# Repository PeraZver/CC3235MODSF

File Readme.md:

# CC3235MODSF Demo Board

Based on the CC3235MODSF LaunchPad Dev Board. The board is based around WiFi module CC3235MODSF, that contains

 - CC3235F MCU
 - 40.0-MHz crystal
 - 32.768-kHz crystal (RTC)
 - 32-Mbit SPI serial flash

## Key features

 - Dual-Band WiFi module CC3235MODSF
 - Onboard 3V3 regulator TLV1117-33
 - Onboard chip antenna M830520 
 - 4-wire JTAG and 2-wire SWD interface
 - Micro-USB connector for power and serial connections over CP2102N
 - Boot mode DIP switch
 - Some LEDs and buttons

Pero, 5/2020

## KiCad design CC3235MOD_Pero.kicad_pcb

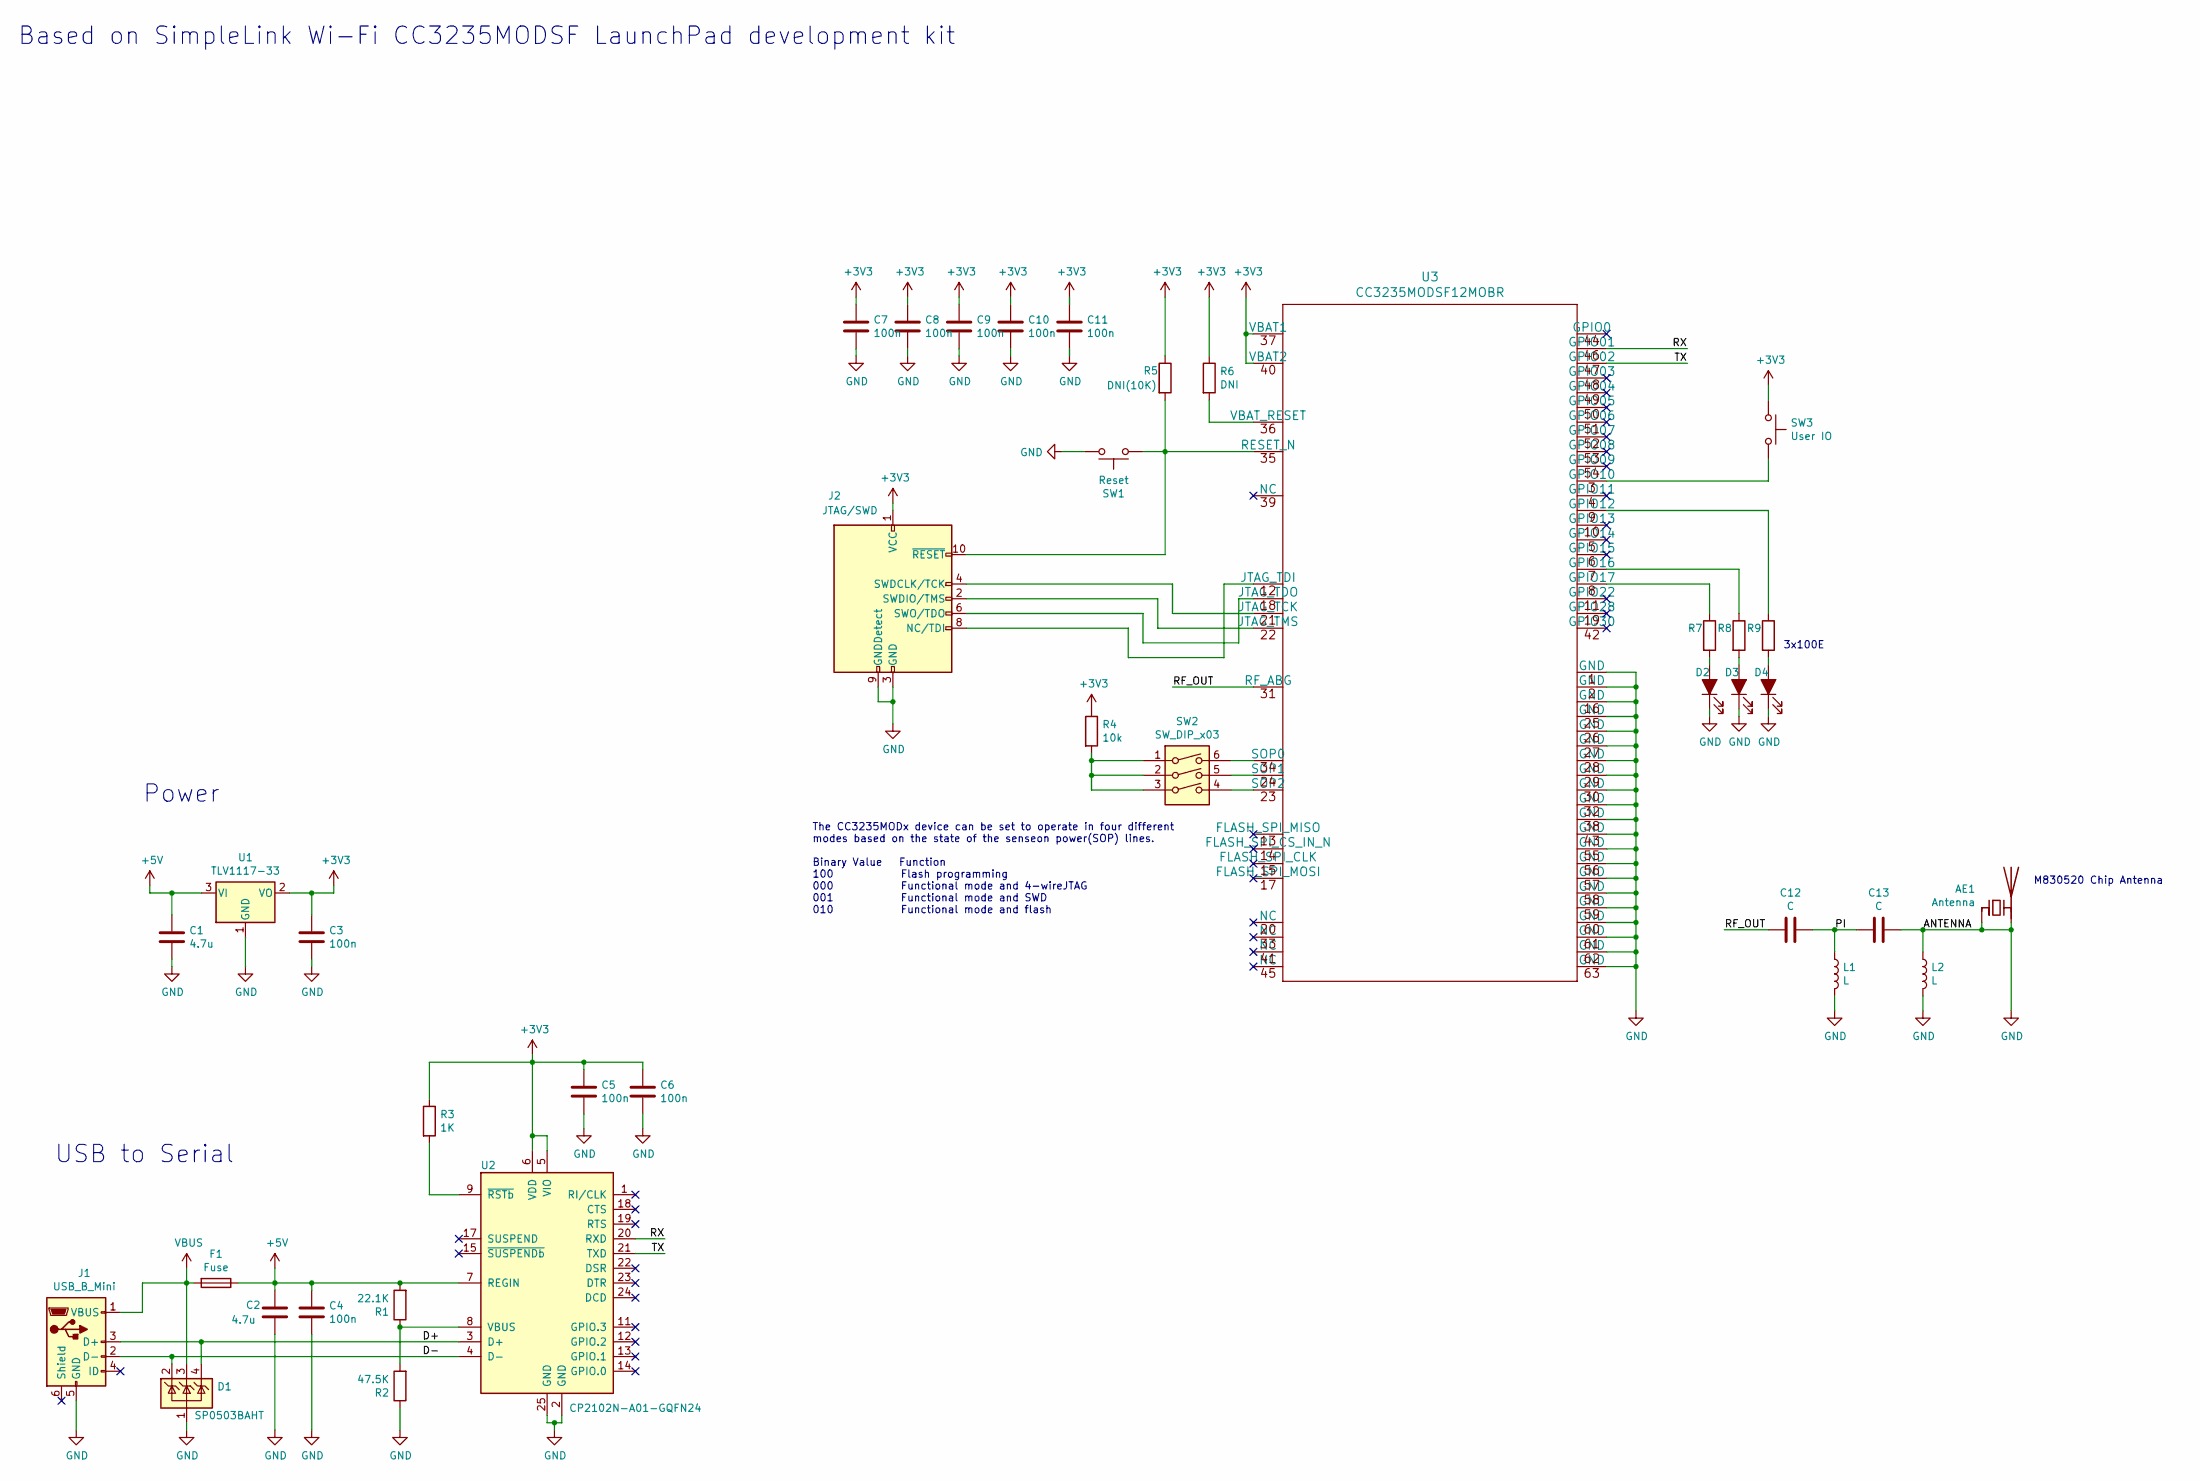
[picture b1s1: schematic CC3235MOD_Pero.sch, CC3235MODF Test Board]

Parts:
AE1: Antenna; M830520
C1, C2: 4.7u; C_0805
C3, C4, C5, C6, C7, C8, C9, C10, C11: 100n; C_0603
C12, C13: C; C_0603_1608Metric
D1: SP0503BAHT; SOT-143
D2, D3, D4: LED_ALT; LED_0603
F1: Fuse; Fuse_SMD1206_Reflow
J1: USB_B_Mini; USB_Micro-B_Molex-105017-0001
J2: JTAG/SWD; Pin_Header_Straight_2x05_Pitch2.54mm
L1, L2: L; L_0603
R1: 22.1K; R_0603
R2: 47.5K; R_0603
R3: 1K; R_0603
R4: 10k; R_0603
R5: DNI(10K); R_0603
R6: DNI; R_0603
R7, R8, R9: 100; R_0603
SW1: Reset; SW_SPST_EVQP0
SW2: SW_DIP_x03; SW_DIP_x3_W8.61mm_Slide_LowProfile
SW3: User IO; SW_SPST_EVQP0
U1: TLV1117-33; SOT-223-3_TabPin2
U2: CP2102N-A01-GQFN24; QFN-24-1EP_4x4mm_Pitch0.5mm
U3: CC3235MODSF12MOBR

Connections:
+3V3: C3.1, C5.1, C6.1, C7.1, C8.1, C9.1, C10.1, C11.1, J2.1 (VCC), R3.1, R4.1, R5.1, R6.1, SW3.1, U1.2 (VO), U2.5 (VIO), U2.6 (VDD), U3.37 (VBAT1), U3.40 (VBAT2)
+5V: C1.1, C2.1, C4.1, F1.1, R1.2, U1.3 (VI), U2.7 (REGIN)
/D+: D1.4 (K), J1.3 (D+), U2.3 (D+)
/D-: D1.2 (K), J1.2 (D-), U2.4 (D-)
/PI: C12.1, C13.2, L1.1
/RF_OUT: C12.2, U3.31 (RF_ABG)
/RX: U2.20 (RXD), U3.46 (GPIO01)
/TX: U2.21 (TXD), U3.47 (GPIO02)
GND: AE1.1 (FEED), AE1.2 (PCB_Trace), C1.2, C2.2, C3.2, C4.2, C5.2, C6.2, C7.2, C8.2, C9.2, C10.2, C11.2, C13.1, D1.1 (A), D2.1 (K), D3.1 (K), D4.1 (K), J1.5 (GND), J2.3 (GND), J2.5 (GND), J2.9 (GNDDetect), L1.2, L2.1, L2.2, R2.1, SW1.1, U1.1 (GND), U2.2 (GND), U2.25 (GND), U3.1 (GND), U3.2 (GND), U3.16 (GND), U3.25 (GND), U3.26 (GND), U3.27 (GND), U3.28 (GND), U3.29 (GND), U3.30 (GND), U3.32 (GND), U3.38 (GND), U3.43 (GND), U3.55 (GND), U3.56 (GND), U3.57 (GND), U3.58 (GND), U3.59 (GND), U3.60 (GND), U3.61 (GND), U3.62 (GND), U3.63 (GND), U3.V
unnamed: D2.2 (A), R7.2
unnamed: D3.2 (A), R8.2
unnamed: D4.2 (A), R9.2
unnamed: J2.2 (SWDIO/TMS), U3.22 (JTAG_TMS)
unnamed: J2.4 (SWDCLK/TCK), U3.21 (JTAG_TCK)
unnamed: J2.6 (SWO/TDO), U3.18 (JTAG_TDO)
unnamed: J2.8 (NC/TDI), U3.12 (JTAG_TDI)
unnamed: J2.10 (~RESET~), R5.2, SW1.2, U3.35 (RESET_N)
unnamed: R1.1, R2.2, U2.8 (VBUS)
unnamed: R3.2, U2.9 (~RSTb)
unnamed: R4.2, SW2.1, SW2.2, SW2.3
unnamed: R6.2, U3.36 (VBAT_RESET)
unnamed: R7.1, U3.8 (GPIO17)
unnamed: R8.1, U3.7 (GPIO16)
unnamed: R9.1, U3.9 (GPIO12)
unnamed: SW2.4, U3.23 (SOP2)
unnamed: SW2.5, U3.24 (SOP1)
unnamed: SW2.6, U3.34 (SOP0)
unnamed: SW3.2, U3.3 (GPIO10)
VBUS: D1.3 (K), F1.2, J1.1 (VBUS)

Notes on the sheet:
M830520 Chip Antenna
The CC3235MODx device can be set to operate in four different modes based on the state of the senseon power(SOP) lines. Binary Value Function 100 Flash programming 000 Functional mode and 4-wireJTAG 001 Functional mode and SWD 010 Functional mode and flash
Based on SimpleLink Wi-Fi CC3235MODSF LaunchPad development kit
USB to Serial
Power
3x100E

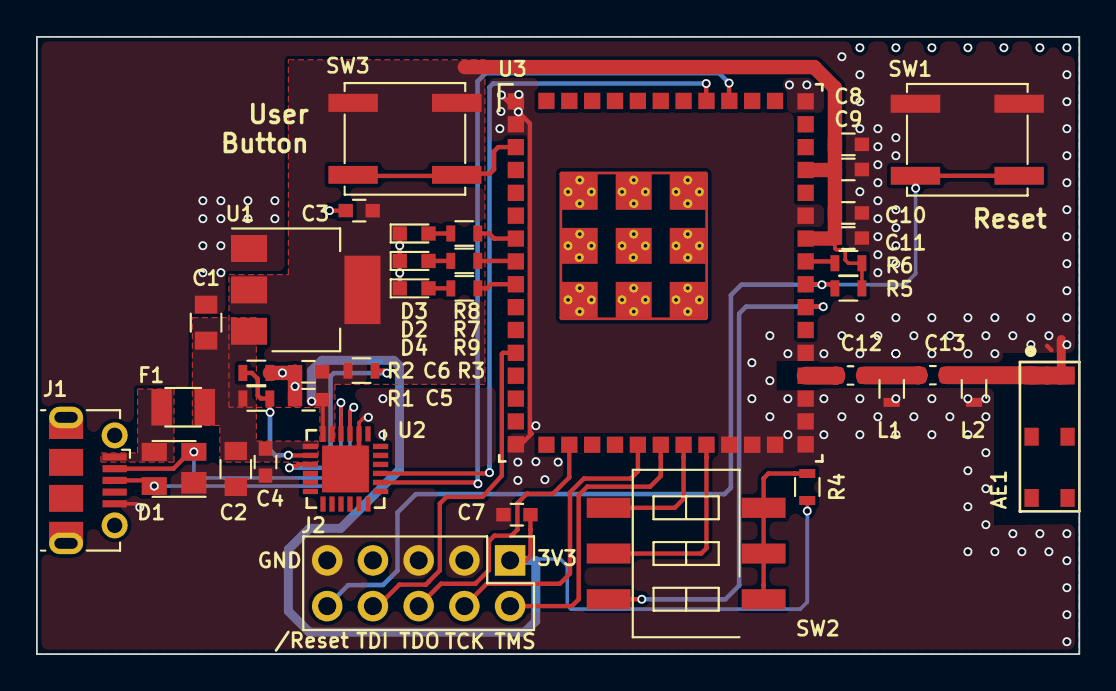
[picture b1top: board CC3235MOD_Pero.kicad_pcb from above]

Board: 2 copper layers, 57.9 x 34.3 mm, 38 parts (0 on the bottom side), 29 nets.

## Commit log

2020-05-20 initial commit, go some symbols
2020-05-20 added some generic components
2020-05-20 added CP2102N for USB connection
2020-05-22 sch finished
2020-05-22 assign footprints, started layout
2020-06-14 antenna footprint done
2020-06-14 placement going
2020-06-18 placement done
2020-06-19 routing 90%
2020-06-19 fixint antenna footprint
2020-06-22 silkscreen references
2020-06-22 keepout on rf trace
2020-06-22 fixed rf filter placement
2020-06-22 antenna gnd solved
2020-06-22 50Ohm trace adapted for 1.6mm PCB
2020-06-22 via stitching
2020-06-22 silkscreen finished, ready to order
2020-06-22 adding a hash number
2020-06-22 SWD silkscreen
2020-08-04 adding readme
2020-08-04 fixed footprint associations AGAIN!
